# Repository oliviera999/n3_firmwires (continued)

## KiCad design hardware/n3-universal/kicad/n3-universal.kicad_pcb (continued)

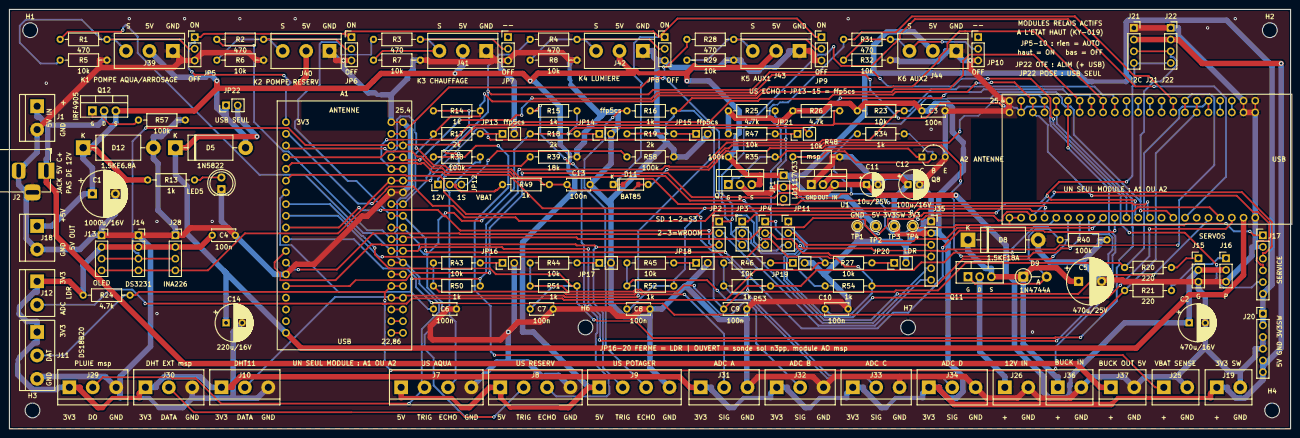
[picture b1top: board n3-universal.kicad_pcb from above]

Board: 2 copper layers, 278.0 x 91.0 mm, 140 parts (0 on the bottom side), 77 nets.

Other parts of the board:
H1, H2, H3, H4, H6, H7: M3; MountingHole_3.2mm_M3

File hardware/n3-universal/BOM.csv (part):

Refs;Qte;Valeur;Empreinte;Description;Source;LCSC;Note achat
A1;1;ESP32 DevKitC 38 broches;ESP32_DevKitC_38pin;Module ESP32-WROOM-32 DevKitC 38 broches, sur 2 supports 1x19 (rangée droite à 25,4 mm, ou 22,86 mm pour un module étroit);;;
A2;1;ESP32-S3-DevKitC-1;ESP32_S3_DevKitC_1_44pin;Site optionnel ESP32-S3-DevKitC-1 44 broches, sur 2 supports 1x22 (rangée droite à 25,4 mm, ou 22,86 mm pour le DevKitC-1 officiel) — un seul module A1 OU A2;Maroc;;Shop4Makers / Moussasoft S3 N16R8 (180 DH) — ne pas importer (ANRT)
C1;1;1000u/16V;CP_Radial_D10.0mm_P5.00mm;Réservoir rail 5V (modules relais + servos + HC-SR04);Maroc;;électrolytique radial
C10;1;100n;C_Disc_D5.0mm_W2.5mm_P5.00mm;Filtre ADC_E;Maroc;;céramique 100 nF
C11;1;10u/25V;CP_Radial_D5.0mm_P2.50mm;Entrée LDO;Maroc;;électrolytique radial
C12;1;100u/16V;CP_Radial_D6.3mm_P2.50mm;Sortie LDO (stabilité LD1117 : >= 10 µF, électrolytique);Maroc;;électrolytique radial
C13;1;100n;C_Disc_D5.0mm_W2.5mm_P5.00mm;Filtre ADC_VBAT;Maroc;;céramique 100 nF
C14;1;220u/16V;CP_Radial_D8.0mm_P3.50mm;Réservoir de VIN_5V derrière D5 (tient le DevKit pendant les creux du rail +5V);Maroc;;électrolytique radial
C2;1;470u/16V;CP_Radial_D8.0mm_P3.50mm;Réservoir du rail 5 V commuté LDO_IN côté servos (appels SG90);Maroc;;électrolytique radial
C3;1;100n;C_Disc_D5.0mm_W2.5mm_P5.00mm;Découplage 3V3 capteurs;Maroc;;céramique 100 nF
C4;1;100n;C_Disc_D5.0mm_W2.5mm_P5.00mm;Découplage 3V3 I2C;Maroc;;céramique 100 nF
C5;1;470u/25V;CP_Radial_D10.0mm_P5.00mm;Réservoir bus 12V protégé;Maroc;;électrolytique radial
C6;1;100n;C_Disc_D5.0mm_W2.5mm_P5.00mm;Filtre ADC ADC_A;Maroc;;céramique 100 nF
C7;1;100n;C_Disc_D5.0mm_W2.5mm_P5.00mm;Filtre ADC ADC_B;Maroc;;céramique 100 nF
C8;1;100n;C_Disc_D5.0mm_W2.5mm_P5.00mm;Filtre ADC ADC_C;Maroc;;céramique 100 nF
C9;1;100n;C_Disc_D5.0mm_W2.5mm_P5.00mm;Filtre ADC ADC_D;Maroc;;céramique 100 nF
D11;1;BAT85;D_DO-35_SOD-123_Dual_P7.62mm;Clamp ADC_VBAT sur +3V3 (panneau branché par erreur sur J25) — empreinte double : BAT85/BAT42/BAT43 DO-35 OU BAT43W/BAT54 SOD-123 (LCSC C19167), un seul des deux posé;import;C19167;"DO-35 épuisé chez LCSC (BAT85 C549292 = 0) → poser la variante SOD-123 BAT43W JSCJ C19167 sur les pads CMS de l'empreinte double ; ou BAT85/BAT42 DO-35 d'une autre source"
D12;1;1.5KE6.8A;D_DO-201AD_P15.24mm_Horizontal;TVS 6,8V (Vrwm 5,8V) sur le rail +5V : surtension / inversion résiduelle;import;C412500;"TVS 6,8 V DO-201 Littelfuse (Vrwm 5,8 V, stock faible) ; repli P6KE6.8A DO-15 C409413 (pattes 0,8 mm, même trou)"
D5;1;1N5822;D_DO-201AD_P15.24mm_Horizontal;"Schottky anti-retour vers VIN du DevKit (K = VIN_5V, A = +5V) — posée sur toutes les cartes ; court-circuitée par le cavalier JP22";Maroc;C2476;"Moussasoft (stock faible) ; LCSC C2476 — une par carte (D5, rev 0.3)"
D8;1;1.5KE18A;D_DO-201AD_P15.24mm_Horizontal;TVS 18V transitoires bus batterie (DO-201 : le P6KE est en DO-15, trop fin);import;C1666858;TVS 18 V DO-201 (Littelfuse 1.5KE18A-B) — PAS de 1.5KE15A locale (conduirait à 14,7 V)
D9;1;1N4744A;D_DO-41_SOD81_P5.08mm_Vertical_AnodeUp;Zener 15V grille-source de Q11 (K=source, A=grille) : VGS borné à -15 V;import;C238928;zener 15 V DO-41
H1 H2 H3 H4 H6 H7;6;M3;MountingHole_3.2mm_M3;Trou de fixation M3;Maroc;;vis M3 + entretoise
J1;1;Bornier_5.08;TerminalBlock_bornier-2_P5.08mm;Entrée 5V alternative (bornier, 1=+5V 2=GND) — protégée contre l'inversion par Q12;Maroc;;KF128 / KF301 pas 5,08 (Moussasoft 4 DH, Shop4Makers)
J10;1;Bornier_5.08;TerminalBlock_bornier-3_P5.08mm;DHT11/DHT22 (1=3V3 2=DATA 3=GND) — fils nus + embouts;Maroc;;KF128 / KF301 pas 5,08 (Moussasoft 4 DH, Shop4Makers)
J11;1;Bornier_5.08;TerminalBlock_bornier-3_P5.08mm;Sonde DS18B20 étanche (1=3V3 2=DATA 3=GND);Maroc;;KF128 / KF301 pas 5,08 (Moussasoft 4 DH, Shop4Makers)
J12;1;Bornier_5.08;TerminalBlock_bornier-2_P5.08mm;LDR déportée entre 3V3 et l'ADC (1=3V3 2=ADC);Maroc;;KF128 / KF301 pas 5,08 (Moussasoft 4 DH, Shop4Makers)
J13;1;Support OLED;PinSocket_1x04_P2.54mm_Vertical;OLED SSD1306 128x64 I2C 0x3C (1=GND 2=VCC 3=SCL 4=SDA);Maroc;;barrette femelle 2,54 sécable (Moussasoft 6 DH)
J14;1;Support I2C ext;PinSocket_1x04_P2.54mm_Vertical;Extension I2C — ex. module DS3231 (1=GND 2=VCC 3=SCL 4=SDA);Maroc;;barrette femelle 2,54 sécable (Moussasoft 6 DH)
J15;1;Header servo;PinHeader_1x03_P2.54mm_Vertical;Servo GROS (1=SIG 2=LDO_IN 3=GND) — rev 0.2.2 : +5V COMMUTE par Q7 (JP1 fermé = permanent);Maroc;;barrette mâle 2,54 sécable (Moussasoft / Shop4Makers)
J16;1;Header servo;PinHeader_1x03_P2.54mm_Vertical;Servo PETITS (1=SIG 2=LDO_IN 3=GND) — rev 0.2.2 : +5V COMMUTE par Q7 (JP1 fermé = permanent);Maroc;;barrette mâle 2,54 sécable (Moussasoft / Shop4Makers)
J17;1;Header service;PinHeader_1x06_P2.54mm_Vertical;Header service (1=3V3 2=GND 3=EN 4=RX0 5=TX0 6=+5V) — tous les autres GPIO sont consommés par la carte universelle;Maroc;;barrette mâle 2,54 sécable (Moussasoft / Shop4Makers)
J18;1;Bornier_5.08;TerminalBlock_bornier-2_P5.08mm;Distribution 5V (1=+5V 2=GND);Maroc;;KF128 / KF301 pas 5,08 (Moussasoft 4 DH, Shop4Makers)
J19;1;Bornier_5.08;TerminalBlock_bornier-2_P5.08mm;Distribution 3V3 capteurs — rail COMMUTE (1=+3V3_SW 2=GND);Maroc;;KF128 / KF301 pas 5,08 (Moussasoft 4 DH, Shop4Makers)
J2;1;Jack 5.5/2.1;BarrelJack_Horizontal;Entrée 5V (jack DC-005 ~2,5 A, centre = +, ouverture bord gauche);Maroc;;jack DC-005 standard
J20;1;Header alim;PinHeader_1x06_P2.54mm_Vertical;Rail Dupont (1-2=+5V 3-4=GND 5-6=+3V3_SW);Maroc;;barrette mâle 2,54 sécable (Moussasoft / Shop4Makers)
J21;1;Support I2C libre;PinSocket_1x04_P2.54mm_Vertical;Port I2C libre 2 (1=GND 2=VCC 3=SCL 4=SDA);Maroc;;barrette femelle 2,54 sécable (Moussasoft 6 DH)
J22;1;Support I2C libre;PinSocket_1x04_P2.54mm_Vertical;Port I2C libre 3 (1=GND 2=VCC 3=SCL 4=SDA);Maroc;;barrette femelle 2,54 sécable (Moussasoft 6 DH)
J25;1;Bornier_5.08;TerminalBlock_bornier-2_P5.08mm;Sonde batterie (1=VBAT+ 2=GND) — 1S ou bus 12V selon profil;Maroc;;KF128 / KF301 pas 5,08 (Moussasoft 4 DH, Shop4Makers)
J26;1;Bornier_5.08;TerminalBlock_bornier-2_P5.08mm;Entrée bus 12V (1=+12V APRES fusible lame externe 7,5-10A 2=GND);Maroc;;KF128 / KF301 pas 5,08 (Moussasoft 4 DH, Shop4Makers)
J28;1;Support I2C libre;PinSocket_1x04_P2.54mm_Vertical;Port I2C libre 4 — INA226 (1=GND 2=VCC 3=SCL 4=SDA);Maroc;;barrette femelle 2,54 sécable (Moussasoft 6 DH)
J29;1;Bornier_5.08;TerminalBlock_bornier-3_P5.08mm;Module pluie DO msp (1=3V3_SW 2=DO 3=GND) — net US1, rôles disjoints;Maroc;;KF128 / KF301 pas 5,08 (Moussasoft 4 DH, Shop4Makers)
J30;1;Bornier_5.08;TerminalBlock_bornier-3_P5.08mm;DHT externe msp (1=3V3_SW 2=DATA 3=GND) — net US2, rôles disjoints;Maroc;;KF128 / KF301 pas 5,08 (Moussasoft 4 DH, Shop4Makers)
J31;1;Bornier_5.08;TerminalBlock_bornier-3_P5.08mm;Entrée analogique ADC_A (1=3V3_SW 2=SIG 3=GND) — LDR msp / sonde sol n3pp;Maroc;;KF128 / KF301 pas 5,08 (Moussasoft 4 DH, Shop4Makers)
J32;1;Bornier_5.08;TerminalBlock_bornier-3_P5.08mm;Entrée analogique ADC_B (1=3V3_SW 2=SIG 3=GND) — LDR msp / sonde sol n3pp;Maroc;;KF128 / KF301 pas 5,08 (Moussasoft 4 DH, Shop4Makers)
J33;1;Bornier_5.08;TerminalBlock_bornier-3_P5.08mm;Entrée analogique ADC_C (1=3V3_SW 2=SIG 3=GND) — LDR msp / sonde sol n3pp;Maroc;;KF128 / KF301 pas 5,08 (Moussasoft 4 DH, Shop4Makers)
J34;1;Bornier_5.08;TerminalBlock_bornier-3_P5.08mm;Entrée analogique ADC_D (1=3V3_SW 2=SIG 3=GND) — LDR msp / sonde sol n3pp;Maroc;;KF128 / KF301 pas 5,08 (Moussasoft 4 DH, Shop4Makers)
J35;1;Support module microSD;PinSocket_1x06_P2.54mm_Vertical;Module microSD SPI 3V3 (1=GND 2=VCC 3=MISO 4=MOSI 5=SCK 6=CS);Maroc;;barrette femelle 2,54 sécable (Moussasoft 6 DH)
J36;1;Bornier_5.08;TerminalBlock_bornier-2_P5.08mm;Vers buck IN (module MP1584/XL4015 sur entretoises : 1=+12V 2=GND);Maroc;;KF128 / KF301 pas 5,08 (Moussasoft 4 DH, Shop4Makers)
J37;1;Bornier_5.08;TerminalBlock_bornier-2_P5.08mm;Depuis buck OUT 5V (1=+5V 2=GND) — protégé contre l'inversion par Q12;Maroc;;KF128 / KF301 pas 5,08 (Moussasoft 4 DH, Shop4Makers)
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
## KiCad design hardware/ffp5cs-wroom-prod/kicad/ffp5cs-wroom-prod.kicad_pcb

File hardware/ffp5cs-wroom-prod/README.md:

# Carte porteuse ffp5cs `wroom-prod` (KiCad)

Plan PCB **généré depuis le code du firmware** `ffp5cs` (env PlatformIO `wroom-prod`,
`-DBOARD_WROOM`) : une **carte porteuse (carrier board)** pour module **ESP32 DevKit V1
30 broches** qui intègre tout le câblage aujourd'hui réalisé « en volant » — relais,
adaptation de niveau des HC-SR04, pull-ups, borniers.

> 🔀 **Bi-module depuis la rev 0.6** : la carte offre un **second site A2** pour un
> **ESP32-S3-DevKitC-1 (44 broches)** — on peuple **UN SEUL** module, A1 (WROOM) **ou**
> A2 (S3). Chaque net fonctionnel touche les deux sites ; côté S3 le firmware se
> compile avec `-DPINMAP_S3_CARRIER` (env `wroom-s3-carrier-test`, section carrier de
> `ffp5cs/include/pins.h`). Source de vérité S3 : `pinmap_s3_carrier.json`. Le header
> **J20** expose les GPIO libres du S3 (dont AUX1=IO47 / AUX2=IO42, pendants de J17).
> ⚠️ Ne PAS flasher un env `carrier` sur le système S3 historique câblé main (ni
> l'inverse) : les cartographies diffèrent (corrections strapping/PSRAM/LED RGB).

```
pinmap.json                  Source de vérité site A1 (broches ← ffp5cs/include/pins.h, section WROOM)
pinmap_s3_carrier.json       Source de vérité site A2 (← pins.h, section PINMAP_S3_CARRIER)
kicad/ffp5cs-wroom-prod.kicad_pro / .kicad_sch / .kicad_pcb   Projet KiCad (format v8, ouvrable KiCad 8/9/10)
BOM.csv                      Nomenclature (séparateur ;)
exports/gerbers-*.zip        Fichiers de fabrication (Gerbers + perçages Excellon)
exports/schema.pdf, pcb-*.svg   Rendus pour revue sans KiCad
fritzing/*.fzz               Vue breadboard du câblage (Fritzing >= 1.0)
generator/generate.py        Régénère schéma + PCB (non routé) + BOM depuis pinmap.json
generator/generate_fritzing.py  Régénère le .fzz de câblage
generator/footprints/        Empreintes officielles KiCad 8.0.9 vendorées (+ empreinte DevKit maison)
tools/check_pinmap_vs_firmware.py   Garde anti-dérive code ↔ plan
```

## Ce que couvre la carte (extrait du firmware)

| Fonction (code) | GPIO | Réalisation sur la carte |
|---|---|---|
| `Pins::POMPE_AQUA` (`actuators.h`, actif HAUT) | 16 | Relais K1 SRD-05 + BC337, bornier NO/COM/NC |
| `Pins::POMPE_RESERV` | 18 | Relais K2, idem |
| `Pins::RADIATEURS` | 2 | Relais K3, idem (strapping → pull-down base) |
| `Pins::LUMIERE` | 15 | Relais K4, idem (strapping) |
| `Pins::SERVO_GROS` | 12 | Header servo J15, série 220 Ω + **pull-down 10k obligatoire** (MTDI) |
| `Pins::SERVO_PETITS` | 13 | Header servo J16, série 220 Ω |
| `Pins::ULTRASON_AQUA/TANK/POTA` (mono-broche TRIG=ECHO, `sensor_ultrasonic.cpp`) | 4 / 19 / 33 | JST 4 pts J7-J9, écho 5 V → 3,3 V par pont 1k/2k |
| `Pins::DHT_PIN` (DHT11, `-DUSE_DHT22` en option) | 27 | JST 3 pts J10 + pull-up 10k |
| `Pins::ONE_WIRE_BUS` (DS18B20) | 26 | Bornier J11 + pull-up 4,7k |
| `Pins::LUMINOSITE` (ADC1, entrée seule) | 34 | Bornier J12 pour LDR déportée + 10k vers GND |
| `Pins::I2C_SDA/SCL` — OLED SSD1306 0x3C (`FEATURE_OLED=1`) | 21 / 22 | Support J13 (GND/VCC/SCL/SDA) + pull-ups 4,7k |
| Extension I2C : **3 ports libres** (DS3231, capteurs…) | 21 / 22 | Supports J14, J18, J19 (même brochage GND/VCC/SCL/SDA) |
| GPIO libres (5, 14, 17, 23, 25, 32, 35) + EN | — | Header J17 |

Alimentation : **5 V / 3 A** (jack 5,5/2,1 centre + OU bornier), condensateur réservoir
1000 µF, LED de présence. Le DevKit est alimenté par VIN **à travers une Schottky
1N5822** : on peut brancher l'USB (flash/debug) alim 5 V connectée sans retour de courant.
Les capteurs logiques (DHT, DS18B20, LDR, OLED) sont sur le **3V3 du DevKit** ;
HC-SR04, servos et relais sur le rail 5 V.

## Choix de conception (et pourquoi)

- **Carrier board plutôt que carte à ESP32 soudé** : le module `esp32dev` reste flashable
  par son USB (`pio run -e wroom-prod -t upload`), remplaçable en 10 s, et on évite tout
  le circuit USB-UART/auto-program. 100 % traversant → soudable à la main, fabricable
  partout (JLCPCB/PCBWay, 2 couches, 150 × 100 mm).
- **Relais commandés actif-HAUT** via NPN : conforme à `actuators.h`
  (`on()` → `digitalWrite(HIGH)`). Ne PAS utiliser un module relais du commerce
  actif-BAS sur ces sorties sans adaptation.
- **Broches de strapping** : GPIO2 et GPIO15 (relais) ont un pull-down 10k sur la base du
  transistor → niveau bas au boot, flash série non perturbé. GPIO12 (MTDI, servo gros) a
  un pull-down 10k dédié (R22) : un niveau haut au boot sélectionnerait un VDD_SDIO à
  1,8 V et **brickerait le démarrage**.
- **HC-SR04 en mono-broche** : le firmware pilote TRIG et lit ECHO sur le même GPIO.
  Câblage par canal : GPIO —(direct)— TRIG ; ECHO —1k— GPIO ; GPIO —2k— GND.
  L'écho 5 V est ramené à ~3,3 V, le trigger 3,3 V est accepté par le capteur alimenté en 5 V.
- **GPIO34 entrée seule, sans pull-up interne** : pont diviseur LDR obligatoire sur la
  carte (LDR déportée entre 3V3 et l'entrée, 10k vers GND).
- **RX0/TX0 laissés libres** (non routés) : réservés à l'USB-UART du module.
- **3 ports I2C libres** (J14/J18/J19) en plus de l'OLED : avec les pull-ups 4,7 k
  déjà en place, 3-4 modules simultanés sont confortables (adresses différentes,
  bus total < ~50 cm) — au-delà, réduire les pull-ups à 2,2 k.

## À vérifier avant fabrication (limites connues)

1. **Entraxe des modules** : l'empreinte A1 suppose un DevKit V1 **30 broches, rangées
   espacées de 25,4 mm** (2 × supports 1×15). Mesurer votre exemplaire ; les variantes
   38 broches (DevKitC) ont un autre brochage → adapter `generate.py` (table `DEVKIT_A/B`).
   L'empreinte A2 suppose un ESP32-S3-DevKitC-1 **44 broches, rangées espacées de
   22,86 mm** (2 × supports 1×22) — vérifier entraxe ET ordre des broches sur
   l'exemplaire réel (tables `S3_LEFT/S3_RIGHT`) avant de souder les supports.
2. **Routage (rev 0.6, dimensionné 12/24 V)** : PCB routé par `generator/route_lv.py`
   (freerouting + vias de couture GND + reliefs thermiques) avec des
   **classes de nets** — contacts relais NO/COM/NC en **2 mm** (≈ 5-6 A continus en
   cuivre 1 oz, marge correcte jusqu'à ~8 A en pointe), rails +5V/VIN/GND en
   **1,2 mm**, signaux 0,4 mm. DRC KiCad 8 : 0 violation, 0 non-connecté ; Gerbers
   dans `exports/`. **Le 230 V reste interdit sur cette carte** (isolement non prévu :
   plans de masse proches des contacts, pas de fentes ni de zone secteur dédiée) —
   la sérigraphie le rappelle près des borniers. Pour du secteur, piloter des modules
   relais/contacteurs 230 V déportés. NB : `generate.py` régénère un PCB **non
   routé** — ne pas régénérer par-dessus `kicad/` sans vouloir perdre le routage.
3. **Relais NO/NC** : mapping issu du couple symbole/empreinte officiel KiCad
   (SANYOU SRD Form C : bobine 2-5, COM 1, NO 3, NC 4). Contrôler à l'ohmmètre au
   premier montage avant de brancher une charge.
4. **ERC/DRC** : les étiquettes locales alimentent les nets (pas de power-flags) ; l'ERC
   émet des avertissements « input power pin not driven », sans conséquence.

## Corrections rev 0.5

- **Supports du DevKit dans la BOM** (ligne « A1 (supports) » : 2 barrettes femelles
  1×15) — jusque-là seulement mentionnés en description.
- **Zone dégagée sous l'antenne WiFi** : keepout cuivre (pistes/vias/pour) sur les
  deux faces sous le débord antenne du module, note sérigraphiée déplacée côté antenne.
- **Checker étendu** : `tools/check_pinmap_vs_firmware.py` fige désormais aussi la
  topologie des canaux HC-SR04 (JST 1=+5V 2=GPIO 3=ECHO 4=GND, 1 k série écho,
  2 k pull-down) — le câblage capteur ne peut plus dériver silencieusement.
- GPIO 23/25 : déclarés `AUX1`/`AUX2` dans `pinmap.json` (firmware ≥ v15.26) ; sur
  cette carte ils restent en breakout J17 (piloter des modules relais externes) —
  les relais AUX embarqués sont sur la variante 230 V.

## Vue Fritzing (câblage de prototype)

`fritzing/ffp5cs-wroom-prod-cablage.fzz` (Fritzing ≥ 1.0) montre le **câblage
breadboard** périphériques ↔ DevKit : HC-SR04 + ponts 1k/2k, DS18B20, LDR, servos,
pull-ups, avec le code couleur rouge = 5 V, orange = 3V3, noir = GND. Le DevKit, le
DHT11, l'OLED et les sorties relais sont figurés par des **headers génériques
étiquetés** (pas de pièce core fidèle dans Fritzing) — survoler une pièce affiche son
titre avec l'ordre des broches. Fichier vérifié à l'ouverture (« Routing completed »,
aucune pièce manquante) ; les positions se réarrangent librement, les connexions
suivent. Le projet KiCad reste la référence pour la fabrication.

## Régénérer / vérifier

```bash
cd hardware/ffp5cs-wroom-prod
python3 generator/generate.py                 # schéma + PCB placé (NON routé) + BOM
python3 generator/route_lv.py                 # routage complet + vérifications
python3 generator/tidy_silkscreen.py   # sérigraphie : repères vs étiquettes
python3 generator/export_fab.py        # zip Gerbers prêt JLCPCB
python3 tools/check_pinmap_vs_firmware.py     # cohérence pins.h (WROOM) ↔ pinmap ↔ schéma ↔ PCB
```

Toute modification de `ffp5cs/include/pins.h` (section WROOM) doit être répercutée dans
`pinmap.json` puis régénérée — le checker échoue (exit ≠ 0) tant que les trois ne sont
pas alignés. ⚠️ La régénération **écrase** `kicad/` : une fois le routage manuel commencé,
faire les retouches dans KiCad et cesser de régénérer (ou porter les retouches dans
`generate.py`).

## Licences

Les empreintes de `generator/footprints/` proviennent de la
[bibliothèque officielle KiCad](https://gitlab.com/kicad/libraries/kicad-footprints)
(tag 8.0.9), licence CC-BY-SA 4.0 avec exception d'usage pour les designs ;
`ESP32_DevKit_V1_30pin.kicad_mod` est généré par `generate.py`.

Commander la carte : voir **[../COMMANDE_JLCPCB.md](../COMMANDE_JLCPCB.md)**.

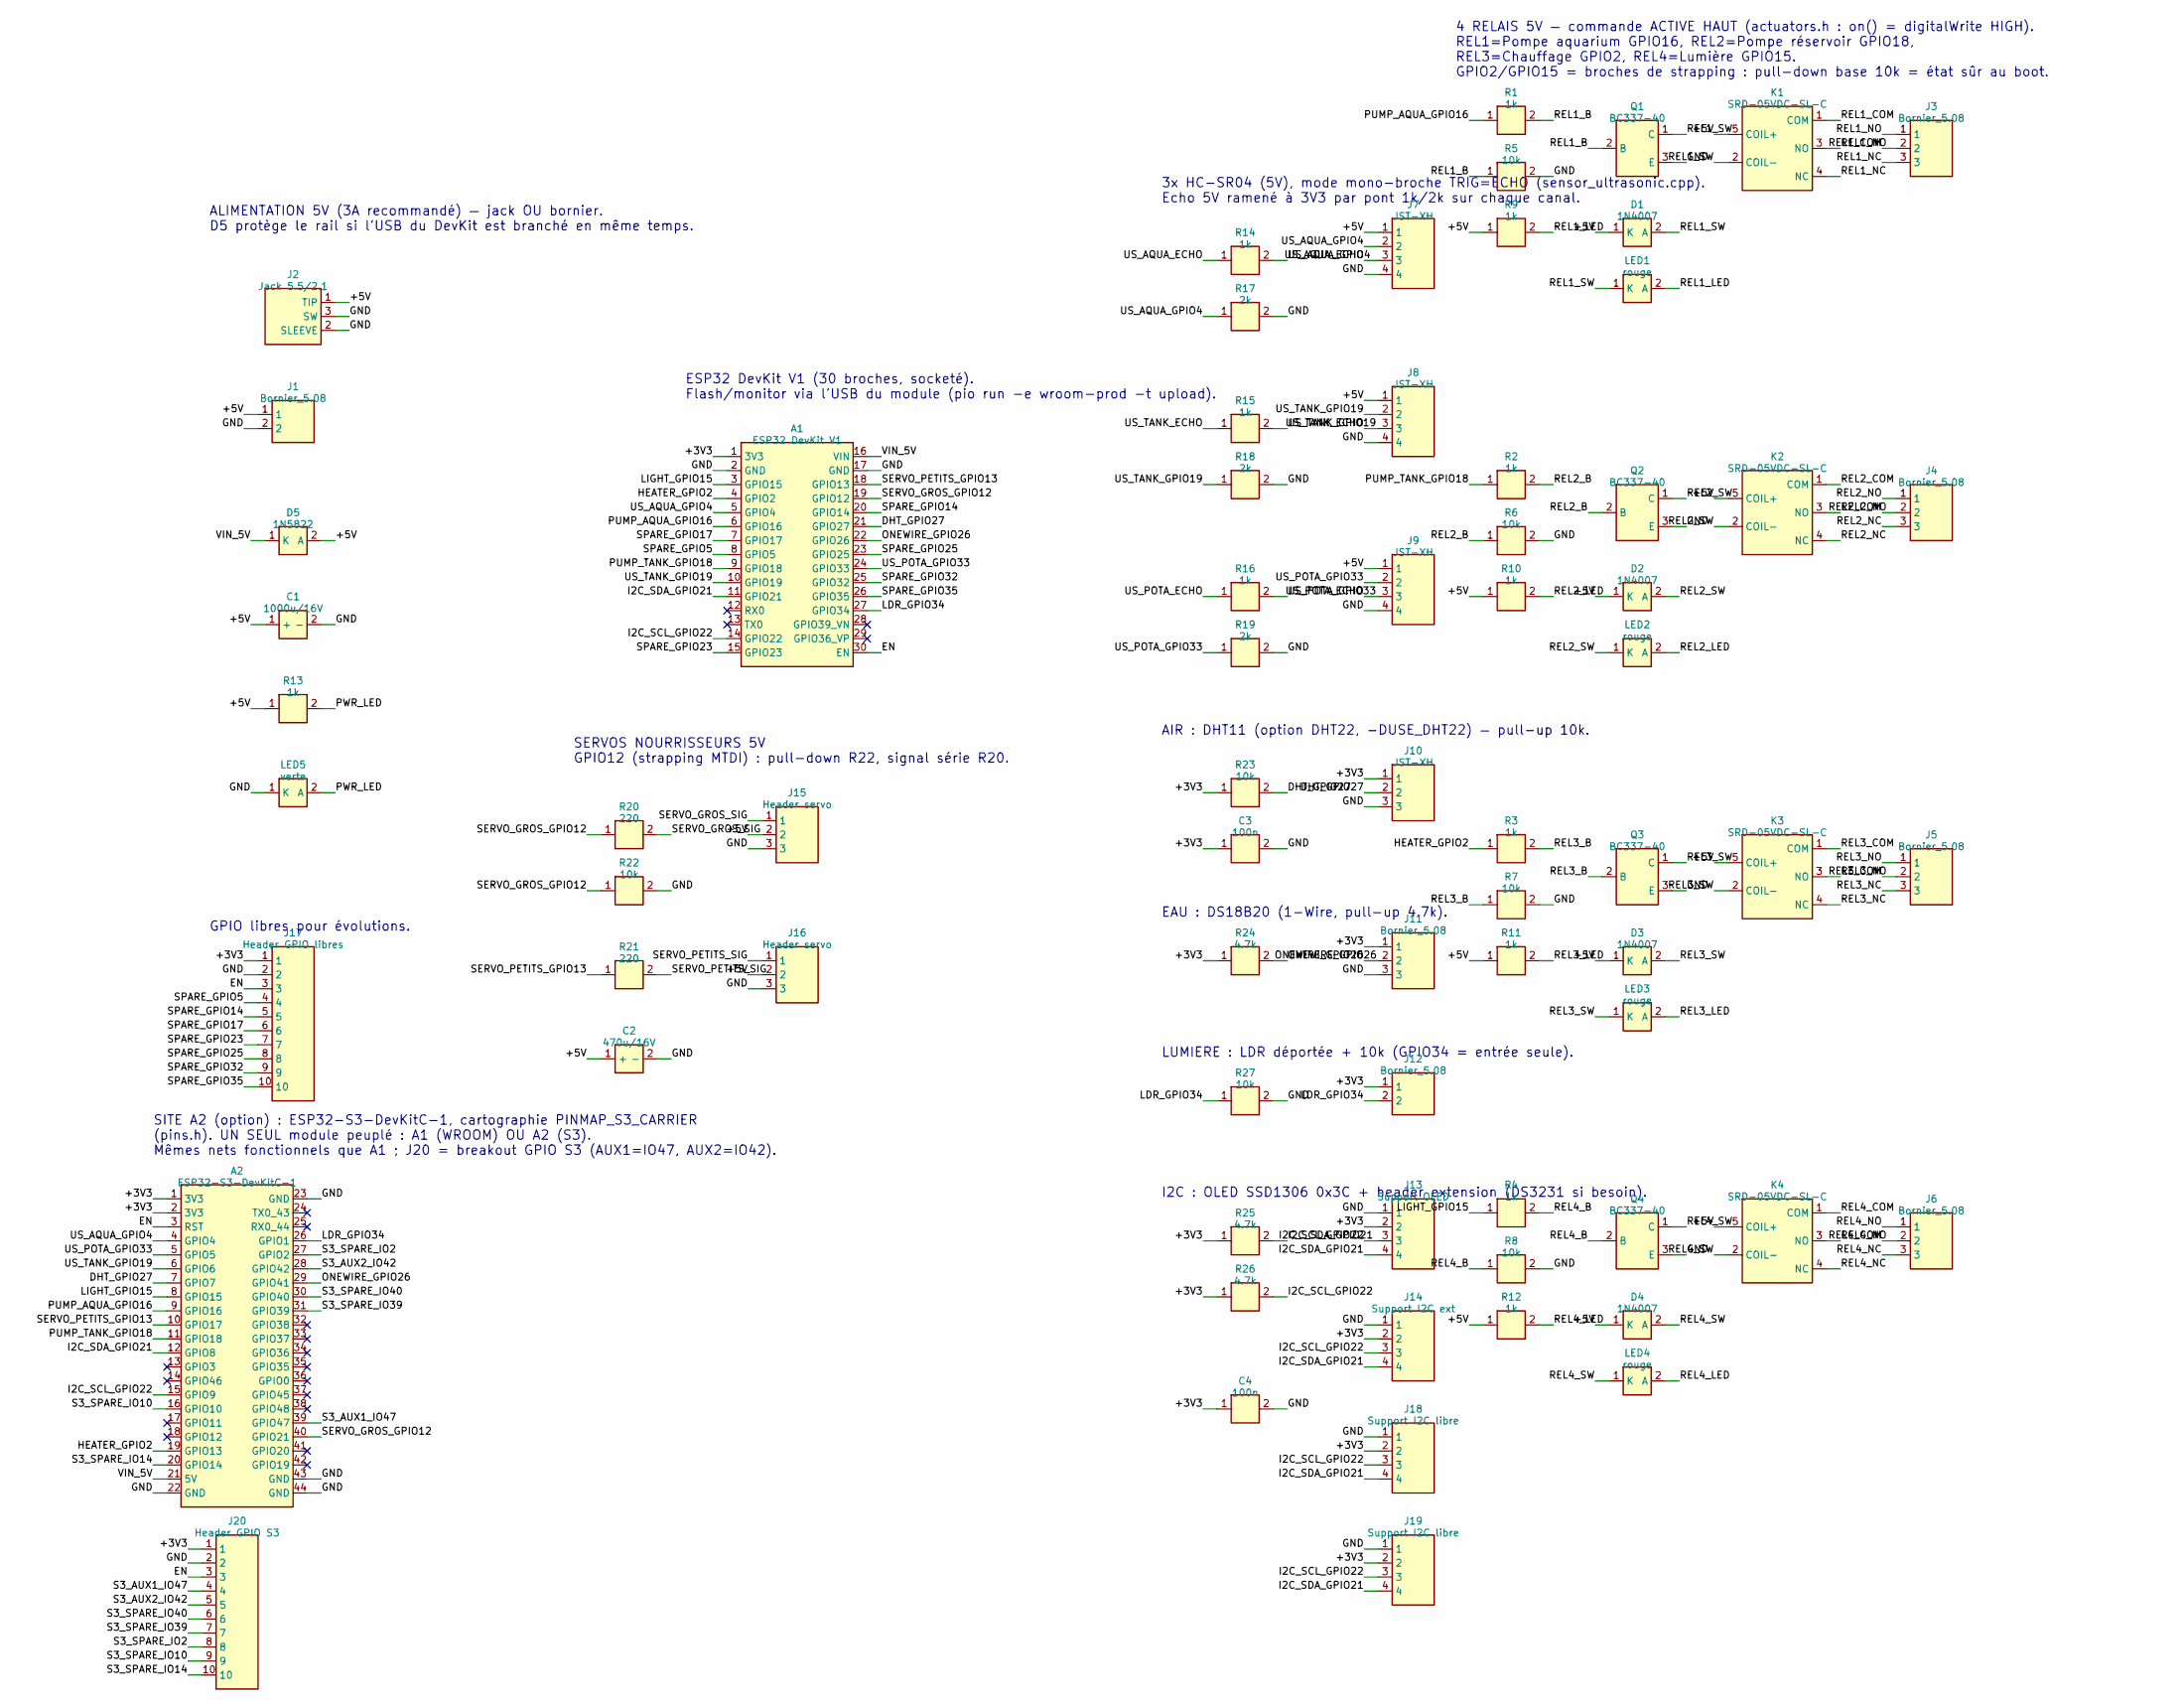
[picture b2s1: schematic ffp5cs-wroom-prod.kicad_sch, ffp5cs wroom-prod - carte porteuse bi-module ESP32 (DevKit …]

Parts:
A1: ESP32 DevKit V1; ESP32_DevKit_V1_30pin
A2: ESP32-S3-DevKitC-1; ESP32_S3_DevKitC_1_44pin
C1: 1000u/16V; CP_Radial_D10.0mm_P5.00mm
C2: 470u/16V; CP_Radial_D8.0mm_P3.50mm
C3, C4: 100n; C_Disc_D5.0mm_W2.5mm_P5.00mm
D1, D2, D3, D4: 1N4007; D_DO-41_SOD81_P10.16mm_Horizontal
D5: 1N5822; D_DO-201AD_P15.24mm_Horizontal
J1, J12: Bornier_5.08; TerminalBlock_bornier-2_P5.08mm
J2: Jack 5.5/2.1; BarrelJack_Horizontal
J3, J4, J5, J6, J11: Bornier_5.08; TerminalBlock_bornier-3_P5.08mm
J7, J8, J9: JST-XH; JST_XH_B4B-XH-A_1x04_P2.50mm_Vertical
J10: JST-XH; JST_XH_B3B-XH-A_1x03_P2.50mm_Vertical
J13: Support OLED; PinSocket_1x04_P2.54mm_Vertical
J14: Support I2C ext; PinSocket_1x04_P2.54mm_Vertical
J15, J16: Header servo; PinHeader_1x03_P2.54mm_Vertical
J17: Header GPIO libres; PinHeader_1x10_P2.54mm_Vertical
J18, J19: Support I2C libre; PinSocket_1x04_P2.54mm_Vertical
J20: Header GPIO S3; PinHeader_1x10_P2.54mm_Vertical
K1, K2, K3, K4: SRD-05VDC-SL-C; Relay_SPDT_SANYOU_SRD_Series_Form_C
LED1, LED2, LED3, LED4: rouge; LED_D5.0mm
LED5: verte; LED_D5.0mm
Q1, Q2, Q3, Q4: BC337-40; TO-92_Inline
R1, R2, R3, R4, R9, R10, R11, R12, R13, R14, R15, R16: 1k; R_Axial_DIN0207_L6.3mm_D2.5mm_P10.16mm_Horizontal
R5, R6, R7, R8, R22, R23, R27: 10k; R_Axial_DIN0207_L6.3mm_D2.5mm_P10.16mm_Horizontal
R17, R18, R19: 2k; R_Axial_DIN0207_L6.3mm_D2.5mm_P10.16mm_Horizontal
R20, R21: 220; R_Axial_DIN0207_L6.3mm_D2.5mm_P10.16mm_Horizontal
R24, R25, R26: 4.7k; R_Axial_DIN0207_L6.3mm_D2.5mm_P10.16mm_Horizontal

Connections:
+3V3: A1.1 (3V3), A2.1 (3V3), A2.2 (3V3), C3.1, C4.1, J10.1, J11.1, J12.1, J13.2, J14.2, J17.1, J18.2, J19.2, J20.1, R23.1, R24.1, R25.1, R26.1
+5V: C1.1 (+), C2.1 (+), D1.1 (K), D2.1 (K), D3.1 (K), D4.1 (K), D5.2 (A), J1.1, J2.1 (TIP), J7.1, J8.1, J9.1, J15.2, J16.2, K1.5 (COIL+), K2.5 (COIL+), K3.5 (COIL+), K4.5 (COIL+), R9.1, R10.1, R11.1, R12.1, R13.1
DHT_GPIO27: A1.21 (GPIO27), A2.7 (GPIO7), J10.2, R23.2
EN: A1.30 (EN), A2.3 (RST), J17.3, J20.3
GND: A1.2 (GND), A1.17 (GND), A2.22 (GND), A2.23 (GND), A2.43 (GND), A2.44 (GND), C1.2 (-), C2.2 (-), C3.2, C4.2, J1.2, J2.2 (SLEEVE), J2.3 (SW), J7.4, J8.4, J9.4, J10.3, J11.3, J13.1, J14.1, J15.3, J16.3, J17.2, J18.1, J19.1, J20.2, LED5.1 (K), Q1.3 (E), Q2.3 (E), Q3.3 (E), Q4.3 (E), R5.2, R6.2, R7.2, R8.2, R17.2, R18.2, R19.2, R22.2, R27.2
HEATER_GPIO2: A1.4 (GPIO2), A2.19 (GPIO13), R3.1
I2C_SCL_GPIO22: A1.14 (GPIO22), A2.15 (GPIO9), J13.3, J14.3, J18.3, J19.3, R26.2
I2C_SDA_GPIO21: A1.11 (GPIO21), A2.12 (GPIO8), J13.4, J14.4, J18.4, J19.4, R25.2
LDR_GPIO34: A1.27 (GPIO34), A2.26 (GPIO1), J12.2, R27.1
LIGHT_GPIO15: A1.3 (GPIO15), A2.8 (GPIO15), R4.1
ONEWIRE_GPIO26: A1.22 (GPIO26), A2.29 (GPIO41), J11.2, R24.2
PUMP_AQUA_GPIO16: A1.6 (GPIO16), A2.9 (GPIO16), R1.1
PUMP_TANK_GPIO18: A1.9 (GPIO18), A2.11 (GPIO18), R2.1
PWR_LED: LED5.2 (A), R13.2
REL1_B: Q1.2 (B), R1.2, R5.1
REL1_COM: J3.2, K1.1 (COM)
REL1_LED: LED1.2 (A), R9.2
REL1_NC: J3.3, K1.4 (NC)
REL1_NO: J3.1, K1.3 (NO)
REL1_SW: D1.2 (A), K1.2 (COIL-), LED1.1 (K), Q1.1 (C)
REL2_B: Q2.2 (B), R2.2, R6.1
REL2_COM: J4.2, K2.1 (COM)
REL2_LED: LED2.2 (A), R10.2
REL2_NC: J4.3, K2.4 (NC)
REL2_NO: J4.1, K2.3 (NO)
REL2_SW: D2.2 (A), K2.2 (COIL-), LED2.1 (K), Q2.1 (C)
REL3_B: Q3.2 (B), R3.2, R7.1
REL3_COM: J5.2, K3.1 (COM)
REL3_LED: LED3.2 (A), R11.2
REL3_NC: J5.3, K3.4 (NC)
REL3_NO: J5.1, K3.3 (NO)
REL3_SW: D3.2 (A), K3.2 (COIL-), LED3.1 (K), Q3.1 (C)
REL4_B: Q4.2 (B), R4.2, R8.1
REL4_COM: J6.2, K4.1 (COM)
REL4_LED: LED4.2 (A), R12.2
REL4_NC: J6.3, K4.4 (NC)
REL4_NO: J6.1, K4.3 (NO)
REL4_SW: D4.2 (A), K4.2 (COIL-), LED4.1 (K), Q4.1 (C)
S3_AUX1_IO47: A2.39 (GPIO47), J20.4
S3_AUX2_IO42: A2.28 (GPIO42), J20.5
S3_SPARE_IO2: A2.27 (GPIO2), J20.8
S3_SPARE_IO10: A2.16 (GPIO10), J20.9
S3_SPARE_IO14: A2.20 (GPIO14), J20.10
S3_SPARE_IO39: A2.31 (GPIO39), J20.7
S3_SPARE_IO40: A2.30 (GPIO40), J20.6
SERVO_GROS_GPIO12: A1.19 (GPIO12), A2.40 (GPIO21), R20.1, R22.1
SERVO_GROS_SIG: J15.1, R20.2
SERVO_PETITS_GPIO13: A1.18 (GPIO13), A2.10 (GPIO17), R21.1
SERVO_PETITS_SIG: J16.1, R21.2
SPARE_GPIO5: A1.8 (GPIO5), J17.4
SPARE_GPIO14: A1.20 (GPIO14), J17.5
SPARE_GPIO17: A1.7 (GPIO17), J17.6
SPARE_GPIO23: A1.15 (GPIO23), J17.7
SPARE_GPIO25: A1.23 (GPIO25), J17.8
SPARE_GPIO32: A1.25 (GPIO32), J17.9
SPARE_GPIO35: A1.26 (GPIO35), J17.10
US_AQUA_ECHO: J7.3, R14.1
US_AQUA_GPIO4: A1.5 (GPIO4), A2.4 (GPIO4), J7.2, R14.2, R17.1
US_POTA_ECHO: J9.3, R16.1
US_POTA_GPIO33: A1.24 (GPIO33), A2.5 (GPIO5), J9.2, R16.2, R19.1
US_TANK_ECHO: J8.3, R15.1
US_TANK_GPIO19: A1.10 (GPIO19), A2.6 (GPIO6), J8.2, R15.2, R18.1
VIN_5V: A1.16 (VIN), A2.21 (5V), D5.1 (K)

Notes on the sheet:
ALIMENTATION 5V (3A recommandé) — jack OU bornier. D5 protège le rail si l'USB du DevKit est branché en même temps.
ESP32 DevKit V1 (30 broches, socketé). Flash/monitor via l'USB du module (pio run -e wroom-prod -t upload).
SERVOS NOURRISSEURS 5V GPIO12 (strapping MTDI) : pull-down R22, signal série R20.
3x HC-SR04 (5V), mode mono-broche TRIG=ECHO (sensor_ultrasonic.cpp). Echo 5V ramené à 3V3 par pont 1k/2k sur chaque canal.
AIR : DHT11 (option DHT22, -DUSE_DHT22) — pull-up 10k.
EAU : DS18B20 (1-Wire, pull-up 4.7k).
LUMIERE : LDR déportée + 10k (GPIO34 = entrée seule).
I2C : OLED SSD1306 0x3C + header extension (DS3231 si besoin).
4 RELAIS 5V — commande ACTIVE HAUT (actuators.h : on() = digitalWrite HIGH). REL1=Pompe aquarium GPIO16, REL2=Pompe réservoir GPIO18, REL3=Chauffage GPIO2, REL4=Lumière GPIO15. GPIO2/GPIO15 = broches de strapping : pull-down base 10k = état sûr au boot.
GPIO libres pour évolutions.
SITE A2 (option) : ESP32-S3-DevKitC-1, cartographie PINMAP_S3_CARRIER (pins.h). UN SEUL module peuplé : A1 (WROOM) OU A2 (S3). Mêmes nets fonctionnels que A1 ; J20 = breakout GPIO S3 (AUX1=IO47, AUX2=IO42).

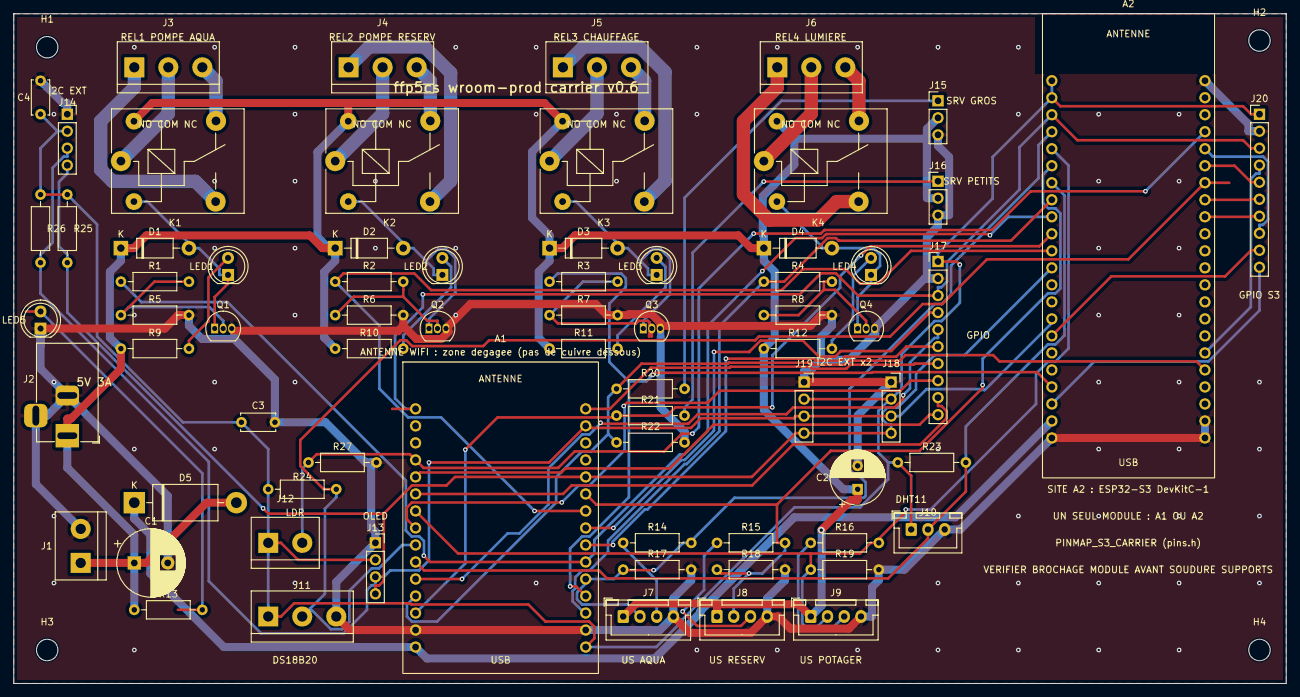
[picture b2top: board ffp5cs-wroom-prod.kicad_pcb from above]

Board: 2 copper layers, 190.0 x 100.0 mm, 75 parts (0 on the bottom side), 63 nets.

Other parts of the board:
H1, H2, H3, H4: M3; MountingHole_3.2mm_M3

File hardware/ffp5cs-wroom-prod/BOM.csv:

Refs;Qte;Valeur;Empreinte;Description
A1;1;ESP32 DevKit V1;ESP32_DevKit_V1_30pin;Module ESP32-WROOM-32 DevKit V1 30 broches, sur 2 supports 1x15
A2;1;ESP32-S3-DevKitC-1;ESP32_S3_DevKitC_1_44pin;Site optionnel ESP32-S3-DevKitC-1 44 broches, sur 2 supports 1x22 (un seul module A1 OU A2)
C1;1;1000u/16V;CP_Radial_D10.0mm_P5.00mm;Réservoir rail 5V (relais + servos + HC-SR04)
C2;1;470u/16V;CP_Radial_D8.0mm_P3.50mm;Découplage rail 5V servos
C3;1;100n;C_Disc_D5.0mm_W2.5mm_P5.00mm;Découplage 3V3 capteurs
C4;1;100n;C_Disc_D5.0mm_W2.5mm_P5.00mm;Découplage 3V3 I2C
D1 D2 D3 D4;4;1N4007;D_DO-41_SOD81_P10.16mm_Horizontal;Diode de roue libre bobine
D5;1;1N5822;D_DO-201AD_P15.24mm_Horizontal;Schottky 3A vers VIN DevKit (anti-retour si USB branché)
H1 H2 H3 H4;4;M3;MountingHole_3.2mm_M3;Trou de fixation M3
J1;1;Bornier_5.08;TerminalBlock_bornier-2_P5.08mm;Entrée 5V alternative (bornier, 1=+5V 2=GND)
J10;1;JST-XH;JST_XH_B3B-XH-A_1x03_P2.50mm_Vertical;DHT11/DHT22 (1=3V3 2=DATA 3=GND)
J11;1;Bornier_5.08;TerminalBlock_bornier-3_P5.08mm;Sonde DS18B20 étanche (1=3V3 2=DATA 3=GND)
J12;1;Bornier_5.08;TerminalBlock_bornier-2_P5.08mm;LDR déportée entre 3V3 et l'ADC (1=3V3 2=ADC)
J13;1;Support OLED;PinSocket_1x04_P2.54mm_Vertical;OLED SSD1306 128x64 I2C 0x3C (1=GND 2=VCC 3=SCL 4=SDA)
J14;1;Support I2C ext;PinSocket_1x04_P2.54mm_Vertical;Extension I2C — ex. module DS3231 (1=GND 2=VCC 3=SCL 4=SDA)
J15;1;Header servo;PinHeader_1x03_P2.54mm_Vertical;Servo GROS (1=SIG 2=+5V 3=GND)
J16;1;Header servo;PinHeader_1x03_P2.54mm_Vertical;Servo PETITS (1=SIG 2=+5V 3=GND)
J17;1;Header GPIO libres;PinHeader_1x10_P2.54mm_Vertical;GPIO libres (1=3V3 2=GND 3=EN 4=IO5 5=IO14 6=IO17 7=IO23 8=IO25 9=IO32 10=IO35)
J18;1;Support I2C libre;PinSocket_1x04_P2.54mm_Vertical;Port I2C libre 2 (1=GND 2=VCC 3=SCL 4=SDA)
J19;1;Support I2C libre;PinSocket_1x04_P2.54mm_Vertical;Port I2C libre 3 (1=GND 2=VCC 3=SCL 4=SDA)
J2;1;Jack 5.5/2.1;BarrelJack_Horizontal;Entrée 5V 3A (jack, centre = +)
J20;1;Header GPIO S3;PinHeader_1x10_P2.54mm_Vertical;GPIO libres site S3 (1=3V3 2=GND 3=EN 4=IO47/AUX1 5=IO42/AUX2 6=IO40 7=IO39 8=IO2 9=IO10 10=IO14)
J3 J4 J5 J6;4;Bornier_5.08;TerminalBlock_bornier-3_P5.08mm;Bornier charge (1=NO 2=COM 3=NC)
J7;1;JST-XH;JST_XH_B4B-XH-A_1x04_P2.50mm_Vertical;HC-SR04 AQUA (1=5V 2=TRIG 3=ECHO 4=GND)
J8;1;JST-XH;JST_XH_B4B-XH-A_1x04_P2.50mm_Vertical;HC-SR04 TANK (1=5V 2=TRIG 3=ECHO 4=GND)
J9;1;JST-XH;JST_XH_B4B-XH-A_1x04_P2.50mm_Vertical;HC-SR04 POTA (1=5V 2=TRIG 3=ECHO 4=GND)
K1 K2 K3 K4;4;SRD-05VDC-SL-C;Relay_SPDT_SANYOU_SRD_Series_Form_C;Relais 5V SPDT 10A (Songle/Sanyou SRD)
LED1 LED2 LED3 LED4;4;rouge;LED_D5.0mm;LED témoin relais ON
LED5;1;verte;LED_D5.0mm;LED présence 5V
Q1 Q2 Q3 Q4;4;BC337-40;TO-92_Inline;Transistor NPN commande relais (1=C 2=B 3=E)
R1 R2 R3 R4;4;1k;R_Axial_DIN0207_L6.3mm_D2.5mm_P10.16mm_Horizontal;Résistance base transistor
R13;1;1k;R_Axial_DIN0207_L6.3mm_D2.5mm_P10.16mm_Horizontal;Résistance LED présence 5V
R14;1;1k;R_Axial_DIN0207_L6.3mm_D2.5mm_P10.16mm_Horizontal;Série écho HC-SR04 AQUA
R15;1;1k;R_Axial_DIN0207_L6.3mm_D2.5mm_P10.16mm_Horizontal;Série écho HC-SR04 TANK
R16;1;1k;R_Axial_DIN0207_L6.3mm_D2.5mm_P10.16mm_Horizontal;Série écho HC-SR04 POTA
R17;1;2k;R_Axial_DIN0207_L6.3mm_D2.5mm_P10.16mm_Horizontal;Pont diviseur écho AQUA (5V->3V3)
R18;1;2k;R_Axial_DIN0207_L6.3mm_D2.5mm_P10.16mm_Horizontal;Pont diviseur écho TANK (5V->3V3)
R19;1;2k;R_Axial_DIN0207_L6.3mm_D2.5mm_P10.16mm_Horizontal;Pont diviseur écho POTA (5V->3V3)
R20;1;220;R_Axial_DIN0207_L6.3mm_D2.5mm_P10.16mm_Horizontal;Série signal servo gros
R21;1;220;R_Axial_DIN0207_L6.3mm_D2.5mm_P10.16mm_Horizontal;Série signal servo petits
R22;1;10k;R_Axial_DIN0207_L6.3mm_D2.5mm_P10.16mm_Horizontal;Pull-down GPIO12 (strapping MTDI : doit être bas au boot)
R23;1;10k;R_Axial_DIN0207_L6.3mm_D2.5mm_P10.16mm_Horizontal;Pull-up data DHT11
R24;1;4.7k;R_Axial_DIN0207_L6.3mm_D2.5mm_P10.16mm_Horizontal;Pull-up bus 1-Wire DS18B20
R25;1;4.7k;R_Axial_DIN0207_L6.3mm_D2.5mm_P10.16mm_Horizontal;Pull-up I2C SDA
R26;1;4.7k;R_Axial_DIN0207_L6.3mm_D2.5mm_P10.16mm_Horizontal;Pull-up I2C SCL
R27;1;10k;R_Axial_DIN0207_L6.3mm_D2.5mm_P10.16mm_Horizontal;Bas du pont diviseur LDR (GPIO34 = entrée seule ADC)
R5 R6 R7 R8;4;10k;R_Axial_DIN0207_L6.3mm_D2.5mm_P10.16mm_Horizontal;Pull-down base (état sûr au boot)
R10 R11 R12 R9;4;1k;R_Axial_DIN0207_L6.3mm_D2.5mm_P10.16mm_Horizontal;Résistance LED témoin
A1 (supports);2;Support femelle 1x15 P2.54;monte sur l'empreinte ESP32_DevKit_V1_30pin;Barrettes femelles 15 pts : le DevKit s'enfiche, jamais soudé
A2 (supports);2;Support femelle 1x22 P2.54;monte sur l'empreinte ESP32_S3_DevKitC_1_44pin;Barrettes femelles 22 pts (site S3 optionnel) : à souder seulement si un S3-DevKitC-1 est prévu
